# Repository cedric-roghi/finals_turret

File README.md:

# finals_turret
A project for the hardware and software of a simple turret replica from the greatest game show on earth, The Finals.

## Table of Contents
- [Requirements](#requirements)
- [Rationale](#rationale)
- [Installation](#installation)
- [Usage](#usage)
- [Features](#features)
- [Future_Additions](#future_additions)
- [Configuration](#configuration)
- [Known_Issues](#known_issues)

## Requirements
- Software:
    - Freecad (for 3D part design)
    - KICAD (PCB design)
    - ST Cube IDE (ST account required for download)
- Hardware:
    - BOM to come
    - Access to a 3D printer

## Rationale
- STM32f411:
    - This is a pretty overkill MCU for a project such as this. It even features I2S protocol which would make it possible for me to replace the dfplayer mini module with my own custom on board audio amplifier. The whole reason to go with this 100MHz MCU is because I want to use it for a drone project so I am testing if it works as expected first with this project. It also makes things faster for the drone project if I can copy and paste the schematic.

## Installation
No code to show yet.

Current Turret design is not great and I should have designed it in pieces to be assembled. Too much support material is needed and its hard to remove without breaking the parts.

Here is the original model from the finals that the project is based on.

And here is my design made in Freecad.

Its not yet optimized for 3D printing but I believe its possible to make small changes to reduce the amount of support without affecting the looks.

FInally here is the brains of the project.

I assembled this PCB by hand using a soldering iron but I would recommend using assembly services from a manufacturer like JLCPCB. Dont forget to use a generous amount of flux if soldering the stm32 by hand.

This is how the PCB should fit into the turret. The whole thing uses M2.5 5mm screws for the speaker mounting and PCB mounting.

The servos mounting positions have mounting holes that should work with the self tapping mounting screws that are usually provided with 9g servos. The servo should be oriented so that the output rotation is in the same axis as the center of rotation for the pan and tilt respectively.

## Usage

## Features
- Audio playback using a dfplayer mini
- Programmable using SWD or USB
- USB serial communications for debugging or remote control
- USB C (2.0)
- Power input 5-12V (can use a normal 12V router power cable)
- Reverse polarity protection
- Buck converter from input stepped down to 5V for efficiency.
- Two PWM output ports to control servo motors.
- Lots of extra exposed MCU pins for rework or future quick additions.
- Potentiometer for volume control

## Future_Additions
- Raspberry pi python code for tracking people with a camera
- New and improved PCB with its own on board audio amplifier + SD card slot or some other form of audio storage

## Configuration

## Known Issues
- The standoff for the dfplayer mini is the wrong way around.
- The port for the USB and barrel jack connector should be at the back and not the side.
- The 3.3V LDO large pin is in fact connected to Vout and not GND. I need to fix the footprint in KiCAD.

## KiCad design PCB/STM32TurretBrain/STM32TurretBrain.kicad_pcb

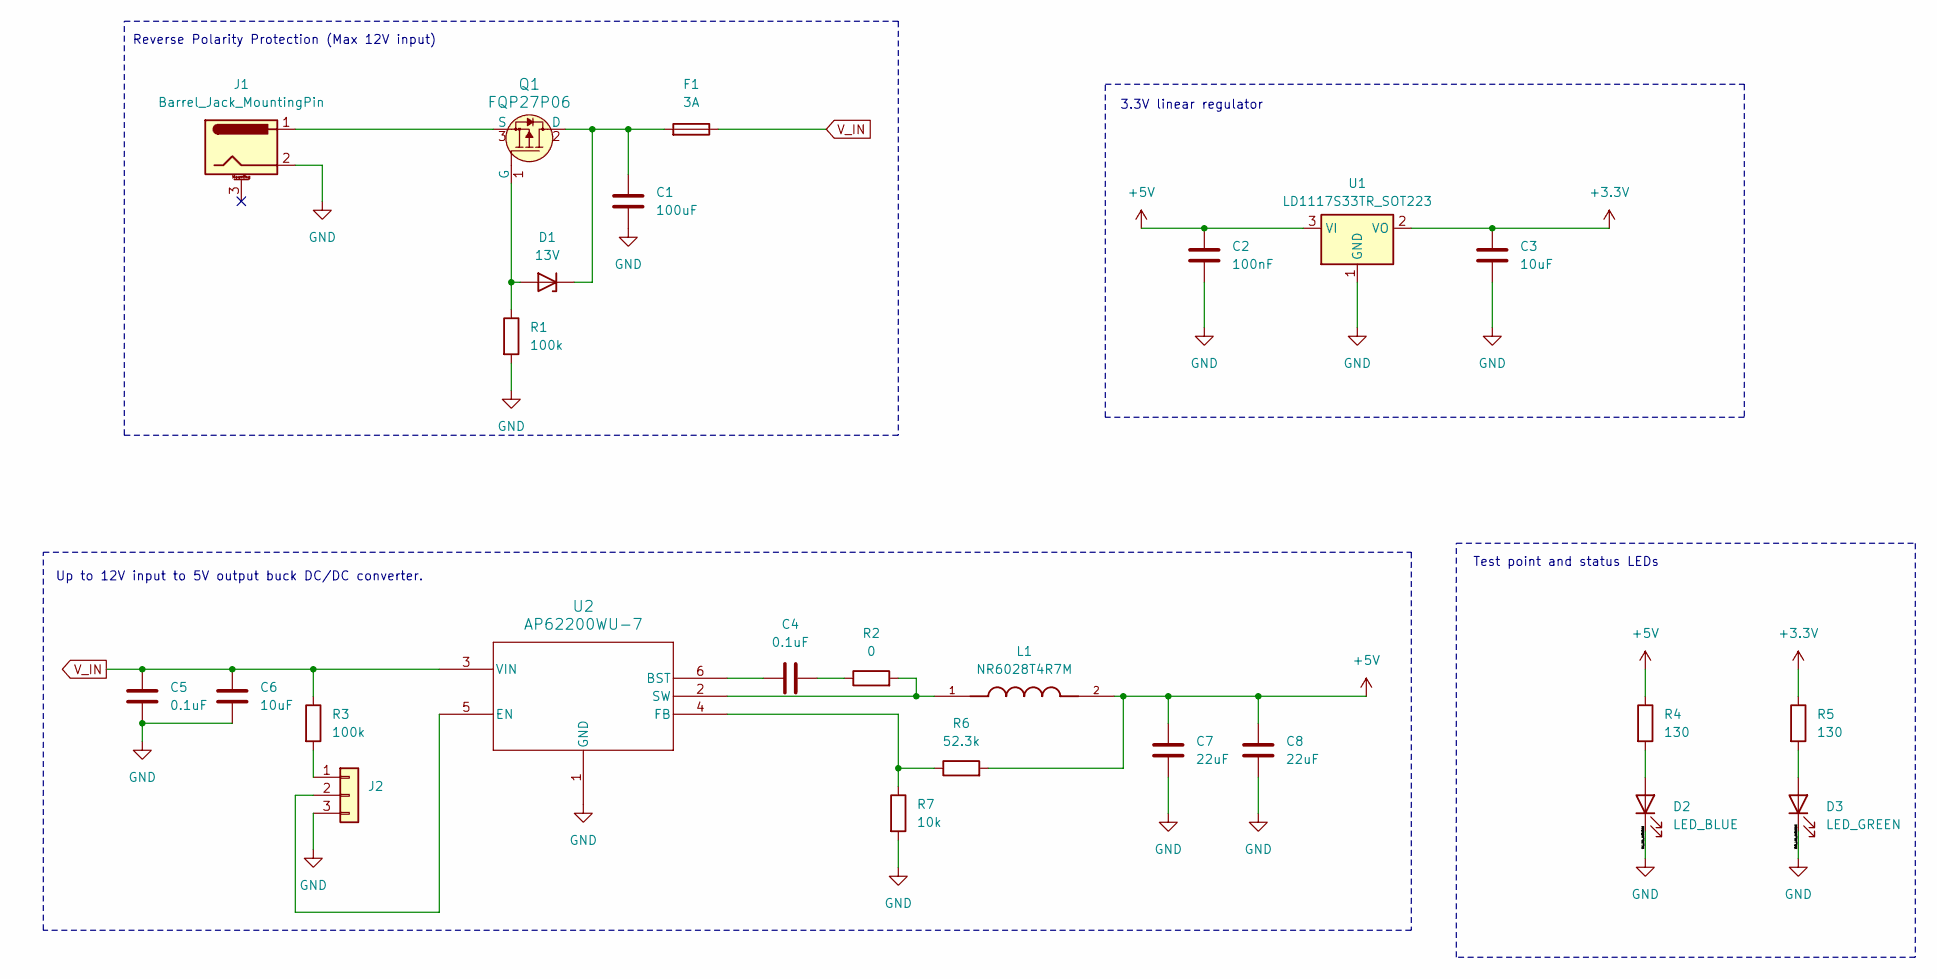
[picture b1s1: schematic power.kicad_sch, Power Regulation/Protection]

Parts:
C1: 100uF; C_Radial_D6.3mm_H5.0mm_P2.50mm
C2: 100nF; C_0603_1608Metric_Pad1.08x0.95mm_HandSolder
C3, C6: 10uF; C_0603_1608Metric_Pad1.08x0.95mm_HandSolder
C4, C5: 0.1uF; C_0603_1608Metric_Pad1.08x0.95mm_HandSolder
C7, C8: 22uF; C_0603_1608Metric_Pad1.08x0.95mm_HandSolder
D1: 13V; Nexperia_CFP3_SOD-123W
D2: LED_BLUE; LED_0603_1608Metric_Pad1.05x0.95mm_HandSolder
D3: LED_GREEN; LED_0603_1608Metric_Pad1.05x0.95mm_HandSolder
F1: 3A; Fuse_0603_1608Metric_Pad1.05x0.95mm_HandSolder
J1: Barrel_Jack_MountingPin; BarrelJack_Horizontal
J2: Conn_01x03; PinHeader_1x03_P2.54mm_Vertical
L1: NR6028T4R7M; IND_NR6028T4R7M
Q1: FQP27P06; TO-220-3; MPN FQP27P06; Digi-Key_PN FQP27P06-ND
R1, R3: 100k; R_0603_1608Metric_Pad0.98x0.95mm_HandSolder
R2: 0; R_0603_1608Metric_Pad0.98x0.95mm_HandSolder
R4, R5: 130; R_0603_1608Metric_Pad0.98x0.95mm_HandSolder
R6: 52.3k; R_0603_1608Metric_Pad0.98x0.95mm_HandSolder
R7: 10k; R_0603_1608Metric_Pad0.98x0.95mm_HandSolder
U1: LD1117S33TR_SOT223; SOT-223
U2: AP62200WU-7; TSOT26-WU_DIO-M

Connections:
+3.3V: C3.1, R5.1, U1.2 (VO); also elsewhere on the board
+5V: C2.1, C7.1, C8.1, L1.2, R4.1, R6.2, U1.3 (VI); also elsewhere on the board
GND: C1.2, C2.2, C3.2, C5.2, C6.2, C7.2, C8.2, D2.1 (K), D3.1 (K), J1.2, J2.3, R1.2, R7.2, U1.1 (GND), U2.1 (GND); also elsewhere on the board
unnamed: C4.2, R2.1
unnamed: D1.2 (A), Q1.1 (G), R1.1
unnamed: C1.1, D1.1 (K), F1.2, Q1.2 (D)
unnamed: D2.2 (A), R4.2
unnamed: D3.2 (A), R5.2
unnamed: J2.1, R3.2
unnamed: J2.2, U2.5 (EN)
unnamed: J1.1, Q1.3 (S)
unnamed: C4.1, U2.6 (BST)
unnamed: R6.1, R7.1, U2.4 (FB)
unnamed: L1.1, R2.2, U2.2 (SW)
V_IN: C5.1, C6.1, F1.1, R3.1, U2.3 (VIN)

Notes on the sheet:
Up to 12V input to 5V output buck DC/DC converter.
3.3V linear regulator
Test point and status LEDs
Reverse Polarity Protection (Max 12V input)

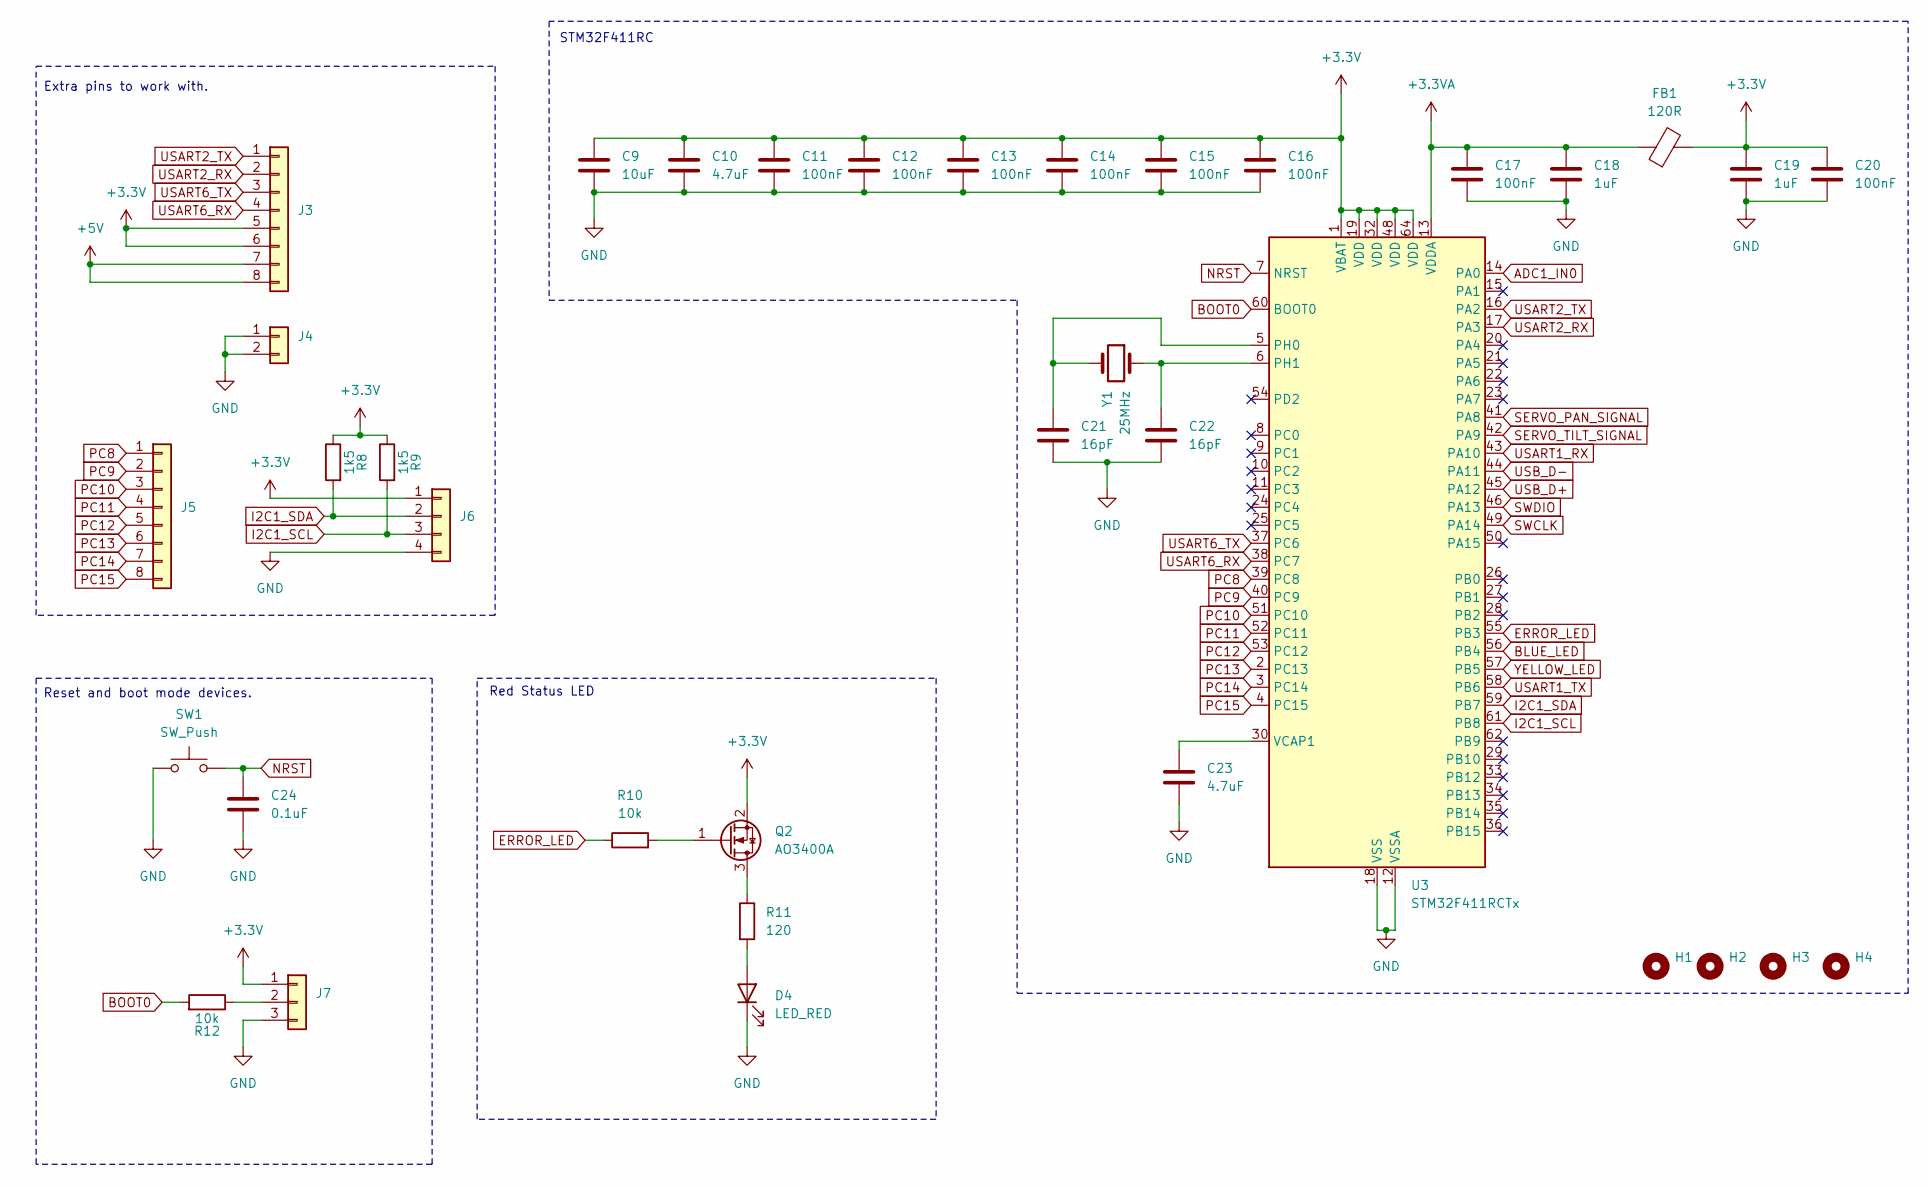
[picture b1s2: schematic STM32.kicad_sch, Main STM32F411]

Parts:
C9: 10uF; C_0603_1608Metric_Pad1.08x0.95mm_HandSolder
C10, C23: 4.7uF; C_0603_1608Metric_Pad1.08x0.95mm_HandSolder
C11, C12, C13, C14, C15, C16, C17, C20: 100nF; C_0603_1608Metric_Pad1.08x0.95mm_HandSolder
C18, C19: 1uF; C_0603_1608Metric_Pad1.08x0.95mm_HandSolder
C21, C22: 16pF; C_0603_1608Metric_Pad1.08x0.95mm_HandSolder
C24: 0.1uF; C_0603_1608Metric_Pad1.08x0.95mm_HandSolder
D4: LED_RED; LED_0603
FB1: 120R; 0603
H1, H2, H3, H4: MountingHole; MountingHole_2.7mm_M2.5_DIN965_Pad
J3, J5: Conn_01x08; PinSocket_1x08_P2.54mm_Vertical
J4: Conn_01x02; PinSocket_1x02_P2.54mm_Vertical
J6: Conn_01x04; PinSocket_1x04_P2.54mm_Vertical
J7: Conn_01x03; PinHeader_1x03_P2.54mm_Vertical
Q2: AO3400A; SOT-23
R8, R9: 1k5; R_0603_1608Metric_Pad0.98x0.95mm_HandSolder
R10, R12: 10k; R_0603_1608Metric_Pad0.98x0.95mm_HandSolder
R11: 120; R_0603_1608Metric_Pad0.98x0.95mm_HandSolder
SW1: SW_Push; SW_SPST_EVQPE1
U3: STM32F411RCTx; LQFP-64_10x10mm_P0.5mm
Y1: 25MHz; XTAL_ECS-250-18-5PX-F-TR

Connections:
+3.3V: C9.1, C10.1, C11.1, C12.1, C13.1, C14.1, C15.1, C16.1, C19.1, C20.1, FB1.2, J3.5, J3.6, J6.1, J7.1, Q2.2 (S), R8.1, R9.1, U3.1 (VBAT), U3.19 (VDD), U3.32 (VDD), U3.48 (VDD), U3.64 (VDD); also elsewhere on the board
+3.3VA: C17.1, C18.1, FB1.1, U3.13 (VDDA)
+5V: J3.7, J3.8; also elsewhere on the board
ADC1_IN0: U3.14 (PA0); also elsewhere on the board
BLUE_LED: U3.56 (PB4); also elsewhere on the board
BOOT0: R12.2, U3.60 (BOOT0)
ERROR_LED: R10.1, U3.55 (PB3)
GND: C9.2, C10.2, C11.2, C12.2, C13.2, C14.2, C15.2, C16.2, C17.2, C18.2, C19.2, C20.2, C21.2, C22.2, C23.2, C24.2, D4.1 (K), J4.1, J4.2, J6.4, J7.3, SW1.1, U3.12 (VSSA), U3.18 (VSS), U3.31 (VSS), U3.47 (VSS), U3.63 (VSS); also elsewhere on the board
I2C1_SCL: J6.3, R9.2, U3.61 (PB8)
I2C1_SDA: J6.2, R8.2, U3.59 (PB7)
NRST: C24.1, SW1.2, U3.7 (NRST)
unnamed: D4.2 (A), R11.2
unnamed: J7.2, R12.1
unnamed: Q2.3 (D), R11.1
unnamed: Q2.1 (G), R10.2
unnamed: C21.1, U3.5 (PH0), Y1.2
unnamed: C22.1, U3.6 (PH1), Y1.1
unnamed: C23.1, U3.30 (VCAP1)
PC8: J5.1, U3.39 (PC8)
PC9: J5.2, U3.40 (PC9)
PC10: J5.3, U3.51 (PC10)
PC11: J5.4, U3.52 (PC11)
PC12: J5.5, U3.53 (PC12)
PC13: J5.6, U3.2 (PC13)
PC14: J5.7, U3.3 (PC14)
PC15: J5.8, U3.4 (PC15)
SERVO_PAN_SIGNAL: U3.41 (PA8); also elsewhere on the board
SERVO_TILT_SIGNAL: U3.42 (PA9); also elsewhere on the board
SWCLK: U3.49 (PA14); also elsewhere on the board
SWDIO: U3.46 (PA13); also elsewhere on the board
USART1_RX: U3.43 (PA10); also elsewhere on the board
USART1_TX: U3.58 (PB6); also elsewhere on the board
USART2_RX: J3.2, U3.17 (PA3)
USART2_TX: J3.1, U3.16 (PA2)
USART6_RX: J3.4, U3.38 (PC7)
USART6_TX: J3.3, U3.37 (PC6)
USB_D+: U3.45 (PA12); also elsewhere on the board
USB_D-: U3.44 (PA11); also elsewhere on the board
YELLOW_LED: U3.57 (PB5); also elsewhere on the board

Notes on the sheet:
Extra pins to work with.
Red Status LED
STM32F411RC
Reset and boot mode devices.

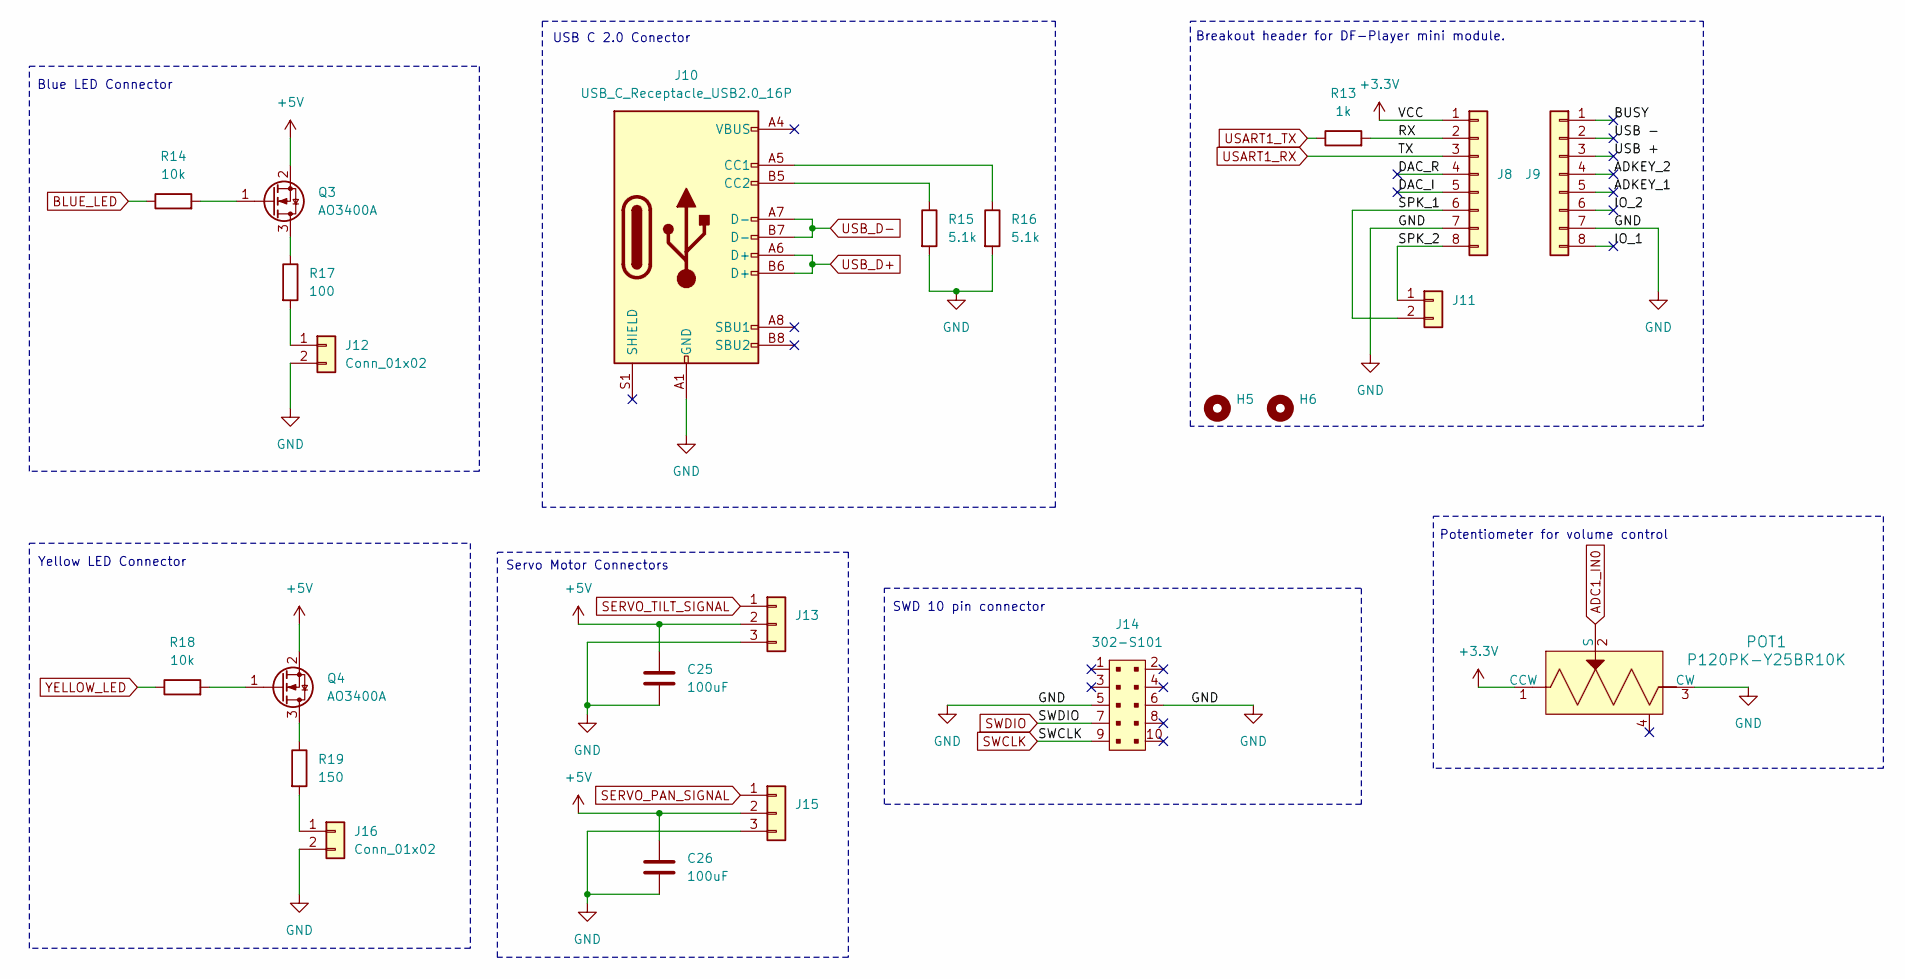
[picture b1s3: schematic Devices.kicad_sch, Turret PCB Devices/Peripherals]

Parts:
C25, C26: 100uF; C_Radial_D6.3mm_H5.0mm_P2.50mm
H5, H6: MountingHole; MountingHole_2.7mm_M2.5_DIN965_Pad
J8, J9: Conn_01x08; PinHeader_1x08_P2.54mm_Vertical
J10: USB_C_Receptacle_USB2.0_16P; USB_C_Receptacle_GCT_USB4105-xx-A_16P_TopMnt_Horizontal
J11: Conn_01x02; PinHeader_1x02_P2.54mm_Vertical
J12, J16: Conn_01x02; PinSocket_1x02_P2.54mm_Vertical
J13, J15: Conn_01x03; PinHeader_1x03_P2.54mm_Vertical
J14: 302-S101; PinHeader_2x5_P2.54mm_Drill1.2mm; MPN 302-S101; Digi-Key_PN ED1543-ND
POT1: P120PK-Y25BR10K; Potentiometer_P120PK-Y25BR10K; MPN P120PK-Y25BR10K; Digi-Key_PN 987-1710-ND
Q3, Q4: AO3400A; SOT-23
R13: 1k; R_0603_1608Metric_Pad0.98x0.95mm_HandSolder
R14, R18: 10k; R_0603_1608Metric_Pad0.98x0.95mm_HandSolder
R15, R16: 5.1k; R_0603_1608Metric_Pad0.98x0.95mm_HandSolder
R17: 100; R_0603_1608Metric_Pad0.98x0.95mm_HandSolder
R19: 150; R_0603_1608Metric_Pad0.98x0.95mm_HandSolder

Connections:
+3.3V: J8.1, POT1.1 (CCW); also elsewhere on the board
+5V: C25.1, C26.1, J13.2, J15.2, Q3.2 (S), Q4.2 (S); also elsewhere on the board
/Devices/ADKEY_1: J9.5
/Devices/ADKEY_2: J9.4
/Devices/BUSY: J9.1
/Devices/DAC_I: J8.5
/Devices/DAC_R: J8.4
/Devices/IO_1: J9.8
/Devices/IO_2: J9.6
/Devices/RX: J8.2, R13.2
/Devices/SPK_1: J8.6, J11.2
/Devices/SPK_2: J8.8, J11.1
/Devices/USB +: J9.3
/Devices/USB -: J9.2
ADC1_IN0: POT1.2 (S); also elsewhere on the board
BLUE_LED: R14.1; also elsewhere on the board
GND: C25.2, C26.2, J8.7, J9.7, J10.A1 (GND), J10.A12 (GND), J10.B1 (GND), J10.B12 (GND), J12.2, J13.3, J14.5, J14.6, J15.3, J16.2, POT1.3 (CW), R15.2, R16.2; also elsewhere on the board
unnamed: J10.A5 (CC1), R16.1
unnamed: J10.B5 (CC2), R15.1
unnamed: J12.1, R17.2
unnamed: J16.1, R19.2
unnamed: Q3.3 (D), R17.1
unnamed: Q3.1 (G), R14.2
unnamed: Q4.3 (D), R19.1
unnamed: Q4.1 (G), R18.2
SERVO_PAN_SIGNAL: J15.1; also elsewhere on the board
SERVO_TILT_SIGNAL: J13.1; also elsewhere on the board
SWCLK: J14.9; also elsewhere on the board
SWDIO: J14.7; also elsewhere on the board
USART1_RX: J8.3; also elsewhere on the board
USART1_TX: R13.1; also elsewhere on the board
USB_D+: J10.A6 (D+), J10.B6 (D+); also elsewhere on the board
USB_D-: J10.A7 (D-), J10.B7 (D-); also elsewhere on the board
YELLOW_LED: R18.1; also elsewhere on the board

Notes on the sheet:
Servo Motor Connectors
USB C 2.0 Conector
Blue LED Connector
Yellow LED Connector
SWD 10 pin connector
Breakout header for DF-Player mini module.
Potentiometer for volume control

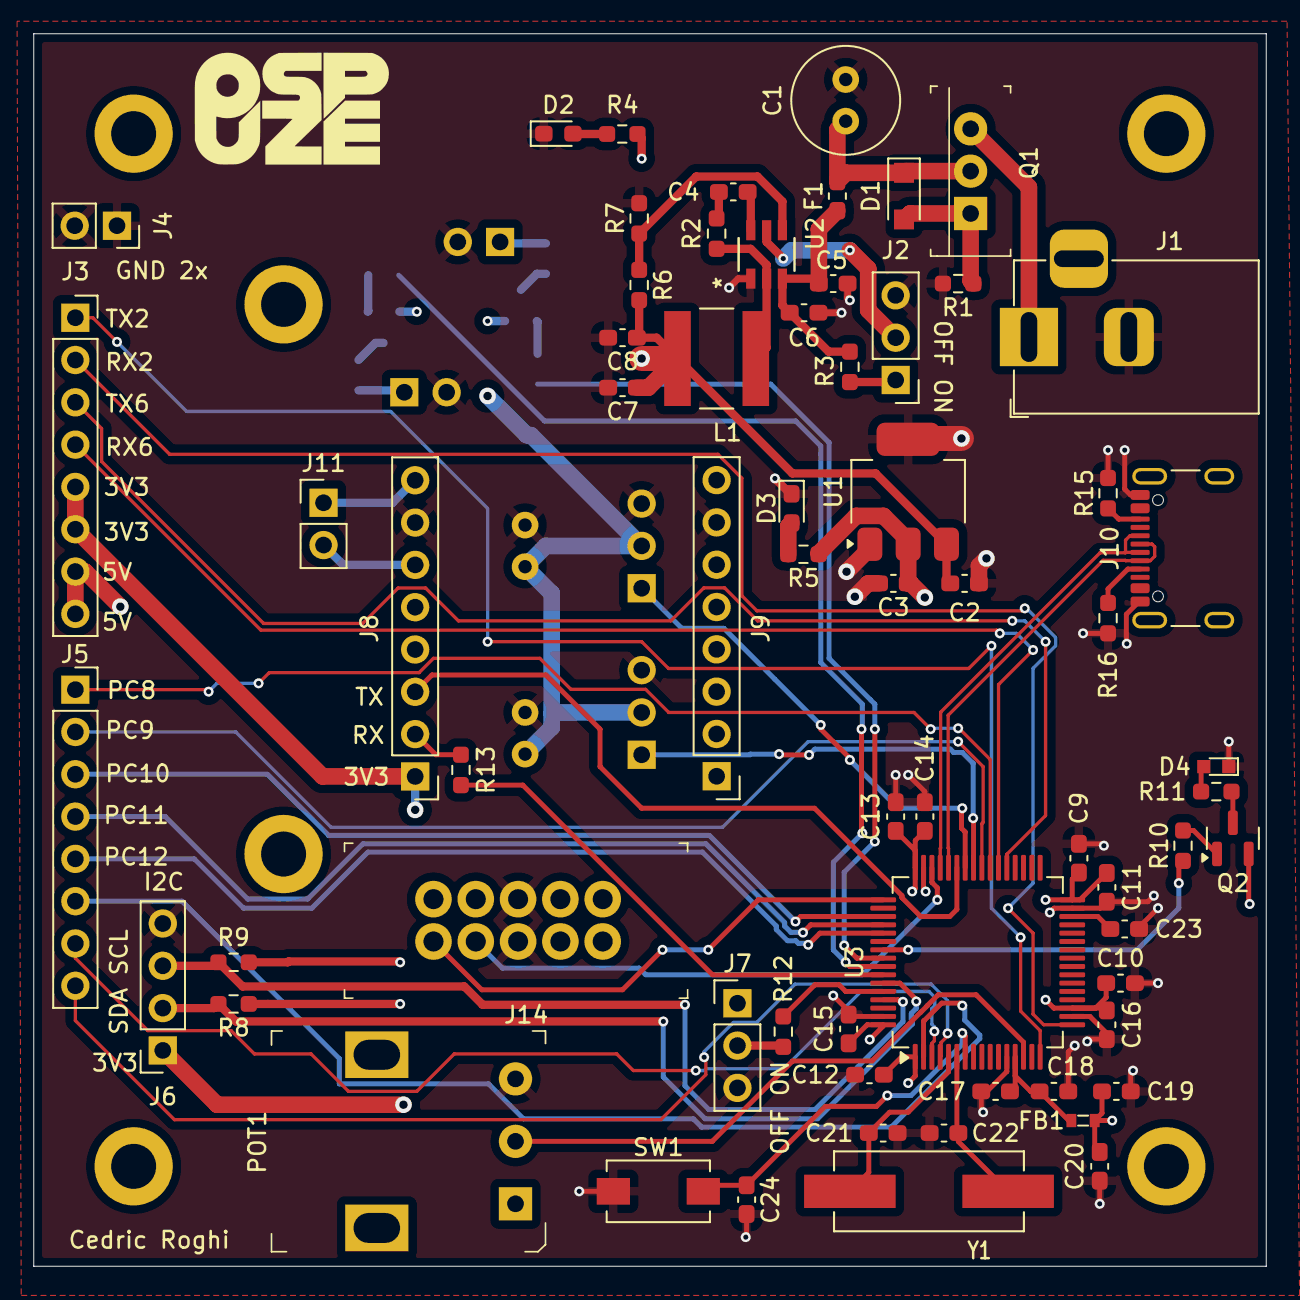
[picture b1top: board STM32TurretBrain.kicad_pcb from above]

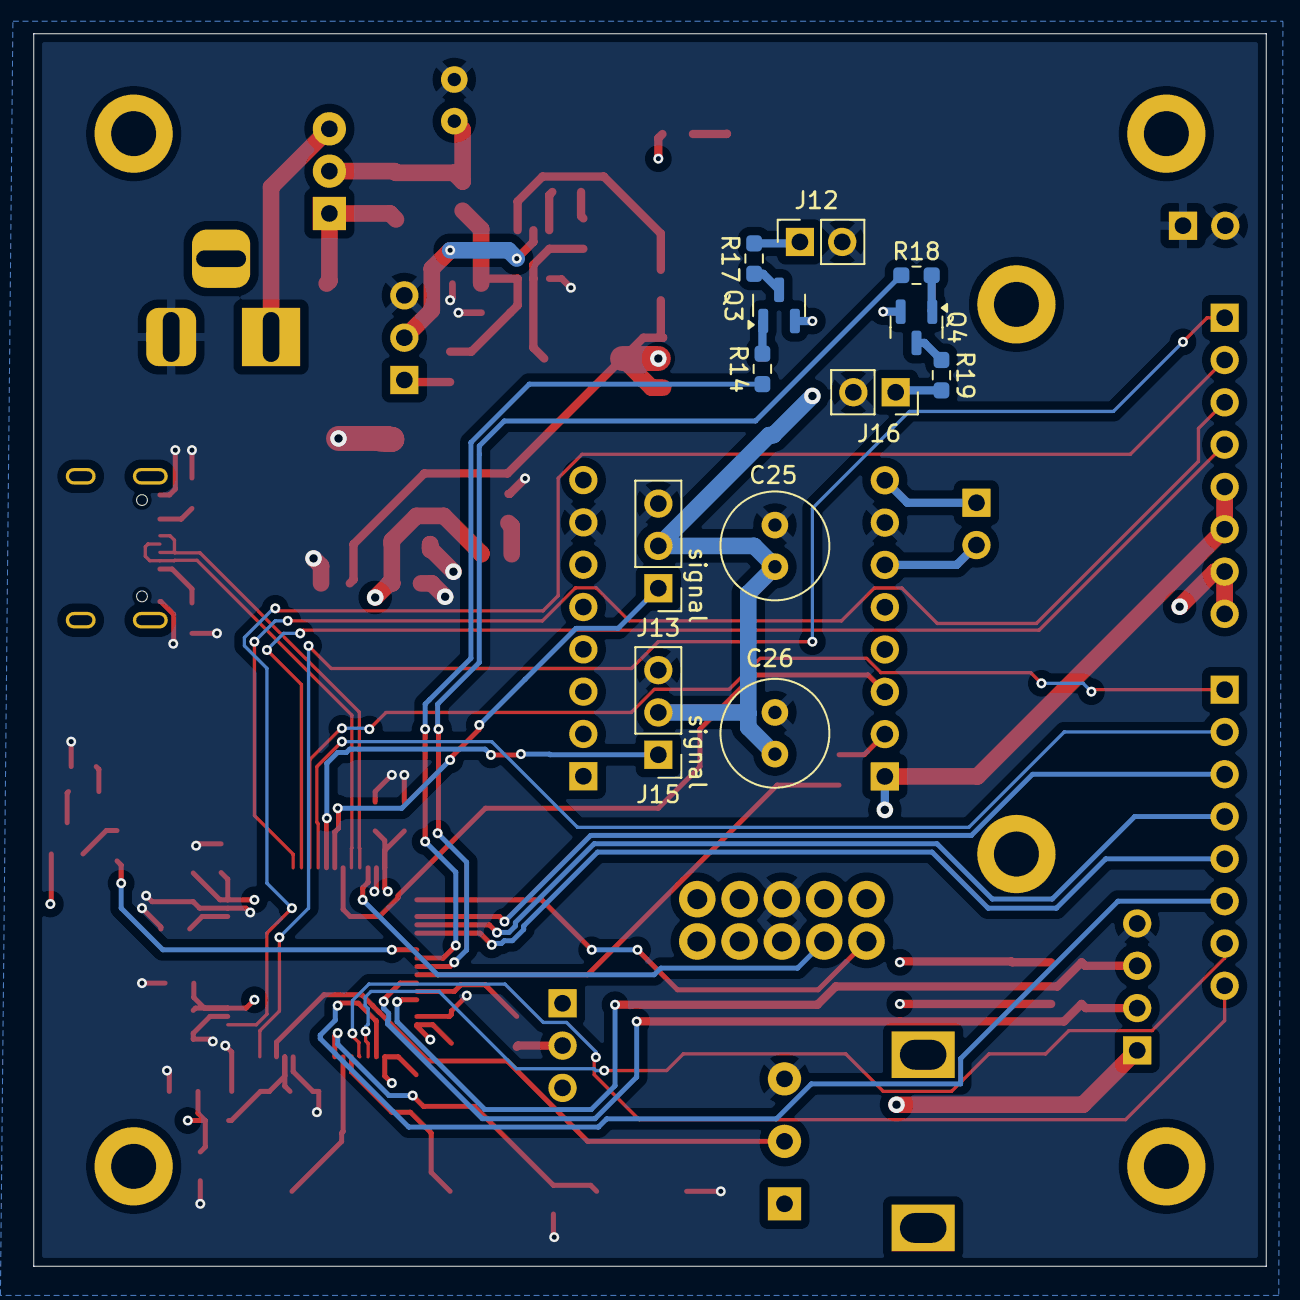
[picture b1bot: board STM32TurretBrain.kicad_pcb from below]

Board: 4 copper layers, 74.0 x 74.0 mm, 84 parts (12 on the bottom side), 62 nets.

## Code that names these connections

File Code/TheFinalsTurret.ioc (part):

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Mcu.Name=STM32F411R(C-E)Tx
Mcu.Package=LQFP64
Mcu.UserName=STM32F411RCTx
PA0-WKUP.Signal=ADCx_IN0
PA10.Mode=Asynchronous
PA10.Signal=USART1_RX
PA11.Mode=Device_Only
PA11.Signal=USB_OTG_FS_DM
PA12.Mode=Device_Only
PA12.Signal=USB_OTG_FS_DP
PA13.Mode=Serial_Wire
PA13.Signal=SYS_JTMS-SWDIO
PA14.Mode=Serial_Wire
PA14.Signal=SYS_JTCK-SWCLK
PA15.Mode=Asynchronous
PA15.Signal=USART1_TX
PA8.Signal=S_TIM1_CH1
PA9.Signal=S_TIM1_CH2
PB3.Signal=GPIO_Output
PB4.Signal=GPIO_Output
PB5.Signal=GPIO_Output
PH0\ -\ OSC_IN.Mode=HSE-External-Oscillator
PH0\ -\ OSC_IN.Signal=RCC_OSC_IN
PH1\ -\ OSC_OUT.Mode=HSE-External-Oscillator
PH1\ -\ OSC_OUT.Signal=RCC_OSC_OUT
RCC.HSE_VALUE=25000000
RCC.SYSCLKFreq_VALUE=96000000
RCC.SYSCLKSource=RCC_SYSCLKSOURCE_PLLCLK
board=custom

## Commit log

2025-08-29 first commit with cad files
2025-09-19 finished PCB V1
2025-09-30 adjusted some freecad files and updated README
2025-10-17 tested servo and pot-meter adc1
